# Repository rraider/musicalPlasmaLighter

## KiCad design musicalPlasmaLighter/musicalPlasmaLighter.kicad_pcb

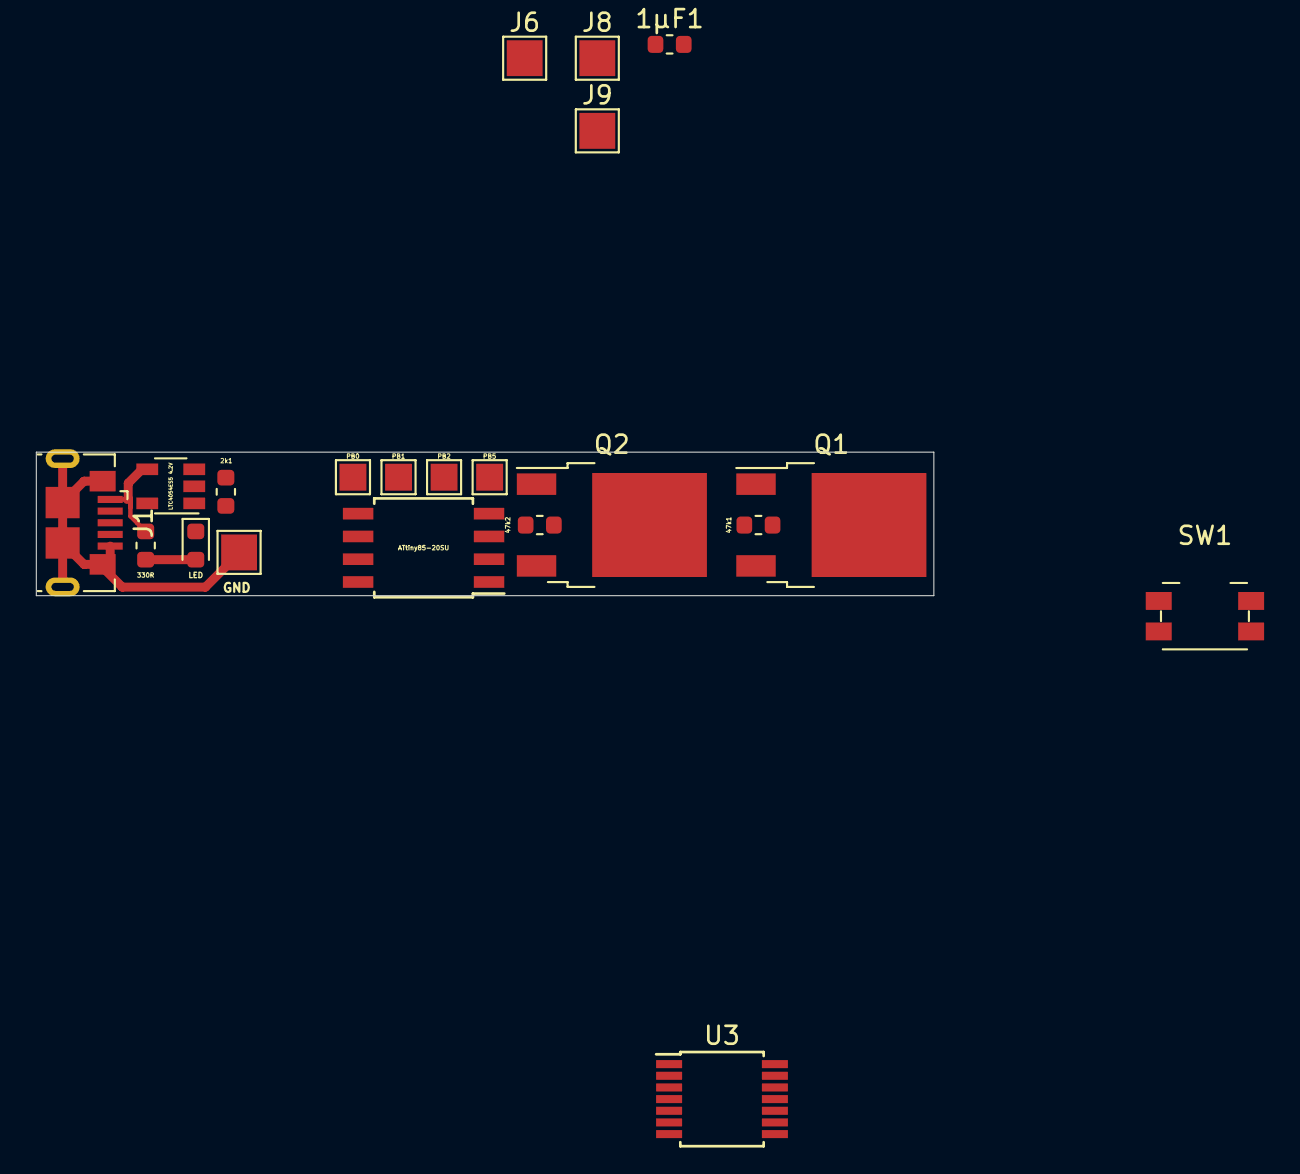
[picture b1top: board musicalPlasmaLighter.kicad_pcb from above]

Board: 2 copper layers, 50.0 x 8.0 mm, 21 parts (0 on the bottom side), 17 nets.

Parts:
1µF1: C; C_0603_1608Metric
2k1, 47k1, 47k2, 330R: R; R_0603_1608Metric
ATtiny85-20SU: ATtiny85-20SU; SOIJ-8_5.3x5.3mm_P1.27mm
GND: Conn_01x01_Male; TestPoint_Pad_2.0x2.0mm
J1: USB_B_Micro; USB_Micro-B_GCT_USB3076-30-A
J6, J8, J9: Conn_01x01_Male; TestPoint_Pad_2.0x2.0mm
LED: LED; LED_0603_1608Metric
LTC4054ES5 4.2V: LTC4054ES5-4.2; TSOT-23-5
PB0, PB1, PB2, PB5: Conn_01x01_Male; TestPoint_Pad_1.5x1.5mm
Q1, Q2: 85N3LH5; TO-252-2
SW1: SW_Push; Panasonic_EVQPUK_EVQPUB
U3: 74HCT00; TSSOP-14_4.4x5mm_P0.65mm

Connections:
+BATT: ATtiny85-20SU.8, SW1.2, U3.14
FET_A: 47k2.2, Q2.1, U3.8
FET_B: 47k1.2, Q1.1, U3.11
GND: 1µF1.2, 2k1.2, 47k1.1, 47k2.1, ATtiny85-20SU.4, GND.1, J1.5, J1.6, LTC4054ES5 4.2V.2, Q1.3, Q2.3, U3.7
unnamed: 2k1.1, LTC4054ES5 4.2V.5
unnamed: 330R.1, LED.2
unnamed: LED.1, LTC4054ES5 4.2V.1
unnamed: ATtiny85-20SU.1, PB5.1
unnamed: ATtiny85-20SU.7, PB2.1
unnamed: J6.1, LTC4054ES5 4.2V.3, SW1.1
unnamed: J8.1, Q1.2
unnamed: J9.1, Q2.2
unnamed: U3.6, U3.9, U3.10
unnamed: U3.3, U3.4, U3.12, U3.13
VCC: 1µF1.1, 330R.2, J1.1, LTC4054ES5 4.2V.4
Vcarrier: ATtiny85-20SU.5, PB0.1, U3.1
Vmod: ATtiny85-20SU.6, PB1.1, U3.2, U3.5

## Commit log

2019-09-07 created new kicad project
2019-09-07 added basic power circuitry
2019-09-09 updated schematics
2019-09-10 updated schemaitcs
2019-09-13 random push
2019-09-13 updated pcb layout
2019-09-17 added source code / initialized PIO
2019-09-17 leo did almost everything
2019-09-26 edited pcb
